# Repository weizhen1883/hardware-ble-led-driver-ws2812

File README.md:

# hardware-ble-led-driver-ws2812

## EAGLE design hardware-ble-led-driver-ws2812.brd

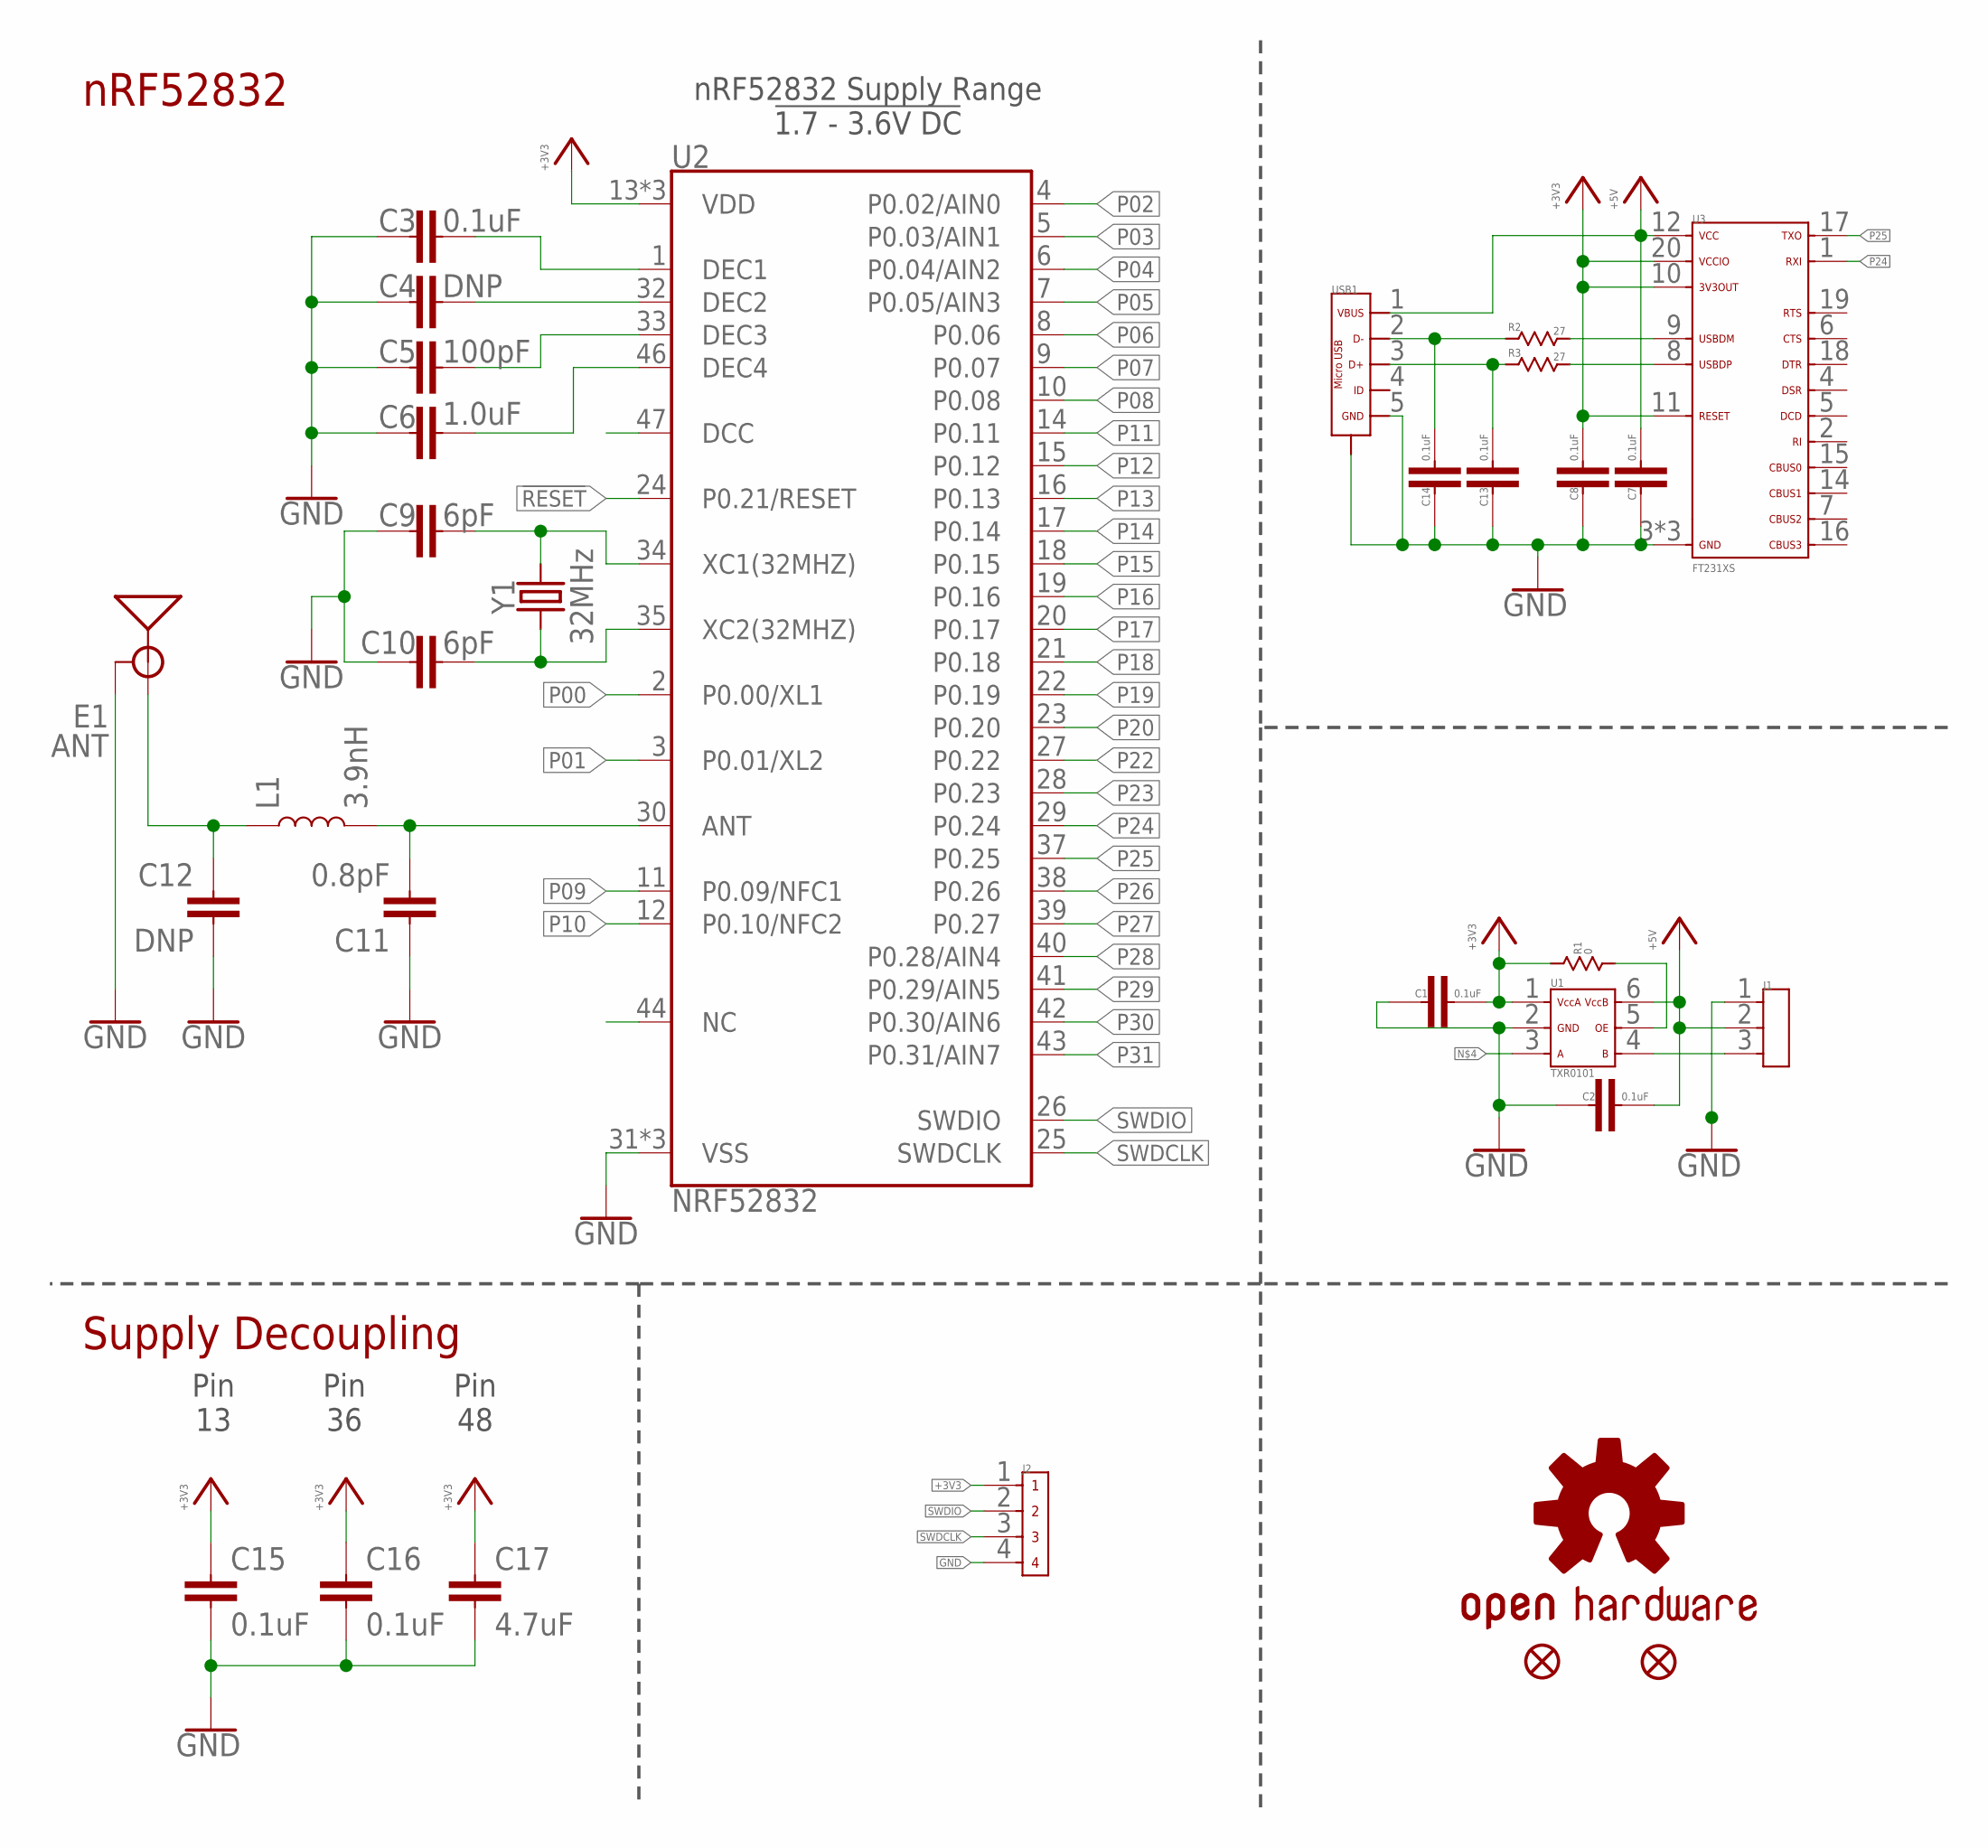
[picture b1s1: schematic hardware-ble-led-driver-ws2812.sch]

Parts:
C1, C2, C3, C7, C8, C13, C14, C15, C16: 0.1uF; 0402
C4, C12: DNP; 0402
C5: 100pF; 0402
C6: 1.0uF; 0402
C9, C10: 6pF; 0402
C11: 0.8pF; 0402
C17: 4.7uF; 0603
E1: ANT; TRACE_ANTENNA_2.4GHZ_15.2MM
FD1, FD2: FIDUCIALUFIDUCIAL; FIDUCIAL-MICRO
J1: 3PIN_HEADER_PITCH2.54MM_TH
J2: 4PIN_HEADER_PITCH1.27MM_TH
L1: 3.9nH; 0402
LOGO1: OSHW-LOGOMINI; OSHW-LOGO-MINI
R1: 0; 0402
R2, R3: 27; 0402
U1: TXB0101-DCK; TSSOP-6
U2: NRF52832; QFN48-6X6MM
U3: FT231XS_WFQFN20; WFQFN-20
USB1: USB-2.0-MICRO_SMD_SMD; MICRO-USB-B-SMD-SMD
Y1: 32MHz; CRYSTAL-SMD-2.0X1.6MM

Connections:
!RESET!: U2.24 (P0.21/RESET)
+3V3: C1.2, C8.2, C15.1, C16.1, C17.1, J2.1, R1.1, U1.1, U2.13 (VDD), U2.36 (VDD), U2.48 (VDD), U3.10 (3V3OUT), U3.11 (RESET), U3.20 (VCCIO)
+5V: C2.2, C7.2, J1.2, U1.6, U3.12 (VCC), USB1.1 (VBUS)
ANT: C11.2, L1.2, U2.30 (ANT)
DCC: U2.47 (DCC)
DEC1: C3.2, U2.1 (DEC1)
DEC2: C4.2, U2.32 (DEC2)
DEC3: C5.2, U2.33 (DEC3)
DEC4: C6.2, U2.46 (DEC4)
GND: C1.1, C2.1, C3.1, C4.1, C5.1, C6.1, C7.1, C8.1, C9.1, C10.2, C11.1, C12.2, C13.1, C14.1, C15.2, C16.2, C17.2, E1.GND, J1.1, J2.4, U1.2, U2.31 (VSS), U2.45 (VSS), U2.EP (VSS), U3.3 (GND), U3.13 (GND), U3.T (GND), USB1.5 (GND), USB1.M1 (SHIELD), USB1.M2 (SHIELD), USB1.M3 (SHIELD), USB1.M4 (SHIELD), USB1.S1 (SHIELD), USB1.S2 (SHIELD)
unnamed: R2.2, U3.9 (USBDM)
unnamed: R1.2, U1.5
unnamed: R3.2, U3.8 (USBDP)
unnamed: J1.3, U1.4
unnamed: C13.2, R3.1, USB1.3 (D+)
unnamed: C14.2, R2.1, USB1.2 (D-)
unnamed: C12.1, E1.ANT (SIGNAL), L1.1
NC: U2.44 (NC)
P00: U2.2 (P0.00/XL1)
P01: U2.3 (P0.01/XL2)
P02: U2.4 (P0.02/AIN0)
P03: U2.5 (P0.03/AIN1)
P04: U2.6 (P0.04/AIN2)
P05: U2.7 (P0.05/AIN3)
P06: U2.8 (P0.06)
P07: U2.9 (P0.07)
P08: U2.10 (P0.08)
P09: U2.11 (P0.09/NFC1)
P10: U2.12 (P0.10/NFC2)
P11: U2.14 (P0.11)
P12: U2.15 (P0.12)
P13: U2.16 (P0.13)
P14: U2.17 (P0.14)
P15: U2.18 (P0.15)
P16: U2.19 (P0.16)
P17: U2.20 (P0.17)
P18: U2.21 (P0.18)
P19: U2.22 (P0.19)
P20: U2.23 (P0.20)
P22: U2.27 (P0.22)
P23: U2.28 (P0.23)
P24: U2.29 (P0.24), U3.1 (RXD)
P25: U2.37 (P0.25), U3.17 (TXD)
P26: U2.38 (P0.26)
P27: U2.39 (P0.27)
P28: U2.40 (P0.28/AIN4)
P29: U2.41 (P0.29/AIN5)
P30: U2.42 (P0.30/AIN6)
P31: U2.43 (P0.31/AIN7)
SWDCLK: J2.3, U2.25 (SWDCLK)
SWDIO: J2.2, U2.26 (SWDIO)
XC1: C9.2, U2.34 (XC1(32MHZ)), Y1.3 (2)
XC2: C10.1, U2.35 (XC2(32MHZ)), Y1.1

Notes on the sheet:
Pin 13
Pin 36
Pin 48
nRF52832
Supply Decoupling
nRF52832 Supply Range !1.7 - 3.6V DC!

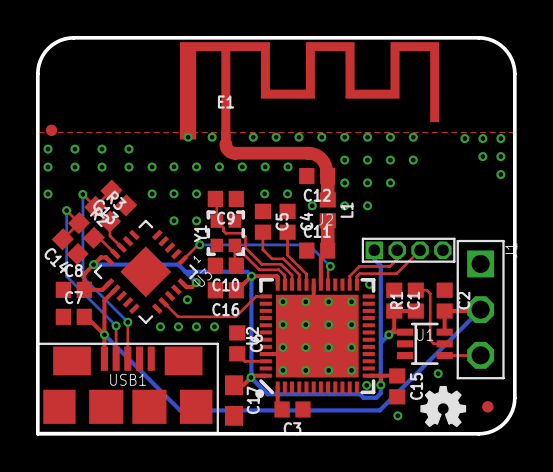
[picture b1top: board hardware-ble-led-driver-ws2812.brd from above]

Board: 2 copper layers, 26.5 x 22.0 mm, 32 parts (0 on the bottom side), 21 nets.

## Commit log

2020-05-25 v1.0.0

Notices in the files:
parts and their libraries:
SparkFun-Aesthetics: Licensing: Creative Commons ShareAlike 4.0 International - https://creativecommons.org/licenses/by-sa/4.0
